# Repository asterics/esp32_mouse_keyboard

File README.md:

# ESP32 Mouse/Keyboard for BLE HID
ESP32 implementation for HID over GATT Keyboard and Mouse (Bluetooth Low Energy). Including serial API for external modules (compatible to Adafruit EZKey HID).

## Compatibility

Due to the wide variety of hardware & software combinations, it is hard to guarantee compatibility.
Nevertheless, we try to test this project with as much devices as possible.

Tested devices by the AsTeRICS team:

|    Device    | Mouse | Keyboard |
|--------------|-------|----------|
|PC with CSR 4.0 BT dongle, Debian Bullseye | yes | yes |
|Lenovo T440s, Debian Buster | yes | yes |
|MacBook Pro (Mid 2012) - macOS Mojave 10.14 | yes | yes |
|PC with CSR 4.0 BT dongle, Win10 Build 2004 | yes | yes |
|Lenovo T440s, Win10 Build 2004 in VirtualBox | no | no |
|Xiaomi Mi A1 - LineageOS 16.0 (Android 9) | yes | yes |
|Asus Nexus 7 (2013) - Android 6.0.1 | yes | yes | 
|iPad Air 2 (MGL12FD/A9 - iOS 13.3.1 | yes (Assistive Touch) | yes (Text input & accessible switch interface) |
|iPad Air 2 (MGL12FD/A9 - iOS 13.5.1 | yes (Assistive Touch) | yes (Text input & accessible switch interface) |
|iPad Pro 10.5" (MPHG2TY/A) - iOS 13.5.1 | yes (Assistive Touch) | yes (Text input & accessible switch interface) |
|iPad 6th Gen (MR7J2FD/A) - iOS 13.5.1 | yes (Assistive Touch) | yes (Text input & accessible switch interface) |

_Note:_ On some iPad devices, there might show up a notification in the Bluetooth menu, that this device may affect WiFi or Bluetooth performance.
You could ignore this error, according to [StackOverflow](https://apple.stackexchange.com/questions/386589/what-does-using-mx-anywhere-2s-may-affect-wi-fi-and-bluetooth-connectivity-mea) there is no clear
reason for this message, maybe it is related to the additional WiFi interface of the ESP32 (other user report this error if a normal mouse has an additional USB-dongle).

_Note:_ If you can report the compatibility status for a device, we would be happy to add a list of community tested devices, just open an issue with the label __device-testreport__.

## Building the ESP32 firmware

Please follow the step-by-step instructions of Espressif's ESP-IDF manual to setup the build infrastructure:
[Setup Toolchain](https://esp-idf.readthedocs.io/en/latest/get-started/index.html#setup-toolchain)

With `idf.py build` or `make` you can build this project.

With `idf.py -p (PORT) flash` or `make flash` you can upload this build to an ESP32

With `idf.py -p (PORT) monitor` or `make monitor` you can see the debug output (please use this output if you open an issue) or trigger basic test commands (mouse movement or a keyboard key press) on
a connected target.

__Note: Currently tested IDF version: release/v5.0 (other ones won't be supported!)__

### esp32miniBT vs. Arduino Nano Connect

This firmware is used on 2 different devices in context of our assistive devices:
* __esp32miniBT module__: This board is located in this repository and is used as addon for v2 FLipMouse, FABI and FLipPad PCBs which use either a TeensyLC or a ProMicro controller.
* __Arduino Nano RP2040 Connect__: Version 3 of FLipMouse and FLipPad (maybe FABI as well) use this Arduino board, where we have a RP2040 controller AND the ESP32 on the same board (more RAM, more flash, cheaper than 2 boards).

__Note:__ Please select the correct type of board in `idf.py menuconfig`!

__Note:__ If you want to use this firmware on a custom board, you can select the external UART interface settings in menuconfig; for our boards the pinning, baudrate and UART config is pre-defined.

# Usage via Console or second UART

## Control via stdin (make monitor)

For basic mouse and keyboard testing, some Bluetooth HID reports can be triggered via the 
keyboard when the make monitor console is running (see Espressif IDF docs: https://docs.espressif.com/projects/esp-idf/en/latest/api-guides/tools/idf-monitor.html ).

|Key|Function   |Description|
|---|-----------|-----------|
|a  |Mouse left |Move mouse left by 30px (`MOUSE_SPEED` define) |
|s  |Mouse down |Move mouse down by 30px (`MOUSE_SPEED` define) |
|d  |Mouse right|Move mouse right by 30px (`MOUSE_SPEED` define) |
|w  |Mouse up   |Move mouse up by 30px (`MOUSE_SPEED` define) |
|l  |Click left |Mouse click right |
|r  |Click right|Mouse click left  |
|q  |Type 'y' (US layout)   |just for testing keyboard reports|

## Control via 2nd UART

This interface is primarily used to control mouse / keyboard activities via an external microcontroller.

### Commands

Each command is started with a '$' character, followed by a command name (uppercase letters) and a variable number of parameters.
A command must be terminated by a '\n' character (LF, ASCII value 10)!

_Note:_ We do not test these on a regular basis!

|Command|Function|Parameters|Description|
|-------|--------|----------|-----------|
|$ID|Get ID|--|Prints out the ID of this module (firmware version number)|
|$GP|Get BLE pairings|--|Prints out all paired devices' MAC adress. The order is used for DP as well, starting with 0|
|$GC|Get active BLE connections|--|Prints out connected paired devices' MAC adress. Ordered by connection occurance (first connected device is listed first)|
|$SW|Switch between devices|BT addr (001122334455)|Switch between connected devices, the given BT addr will receive the HID packets|
|$DP|Delete one pairing (or all) |number of pairing, given as ASCII-characer '0'-'9'|Deletes one pairing. The pairing number is determined by the command GP. If no parameter is given, all pairings are removed!|
|$PM|Set pairing mode|'0' / '1'|Enables (1) or disables (0) discovery/advertising and terminates an exisiting connection if enabled|
|$NAME|Set BLE device name|name as ASCII string|Set the device name to the given name. Restart required.|
|$UG|Initiating firmware update|--|Boot partition is set to 'factory', if available. Device is restarted and expects firmware (.bin) via UART2|
|$SV|Set a key/value pair |key value| Set a value to ESP32 NVS storage, e.g. "$SV testkey This is a testvalue". Note: no spaces in the key! Returns "OK xx/yy used/free" on success, NVS:"error code" otherwise.|
|$GV|Get a key/value pair |key| Get a value from ESP32 NVS storage, e.g. "$GV testkey". Note: no spaces in the key!|
|$CV|Clear all key/value pairs |--| Delete all stored key/value pairs from $SV.|

### HID input

We use a format which is compatible to the Adafruit EZKey module, and added a few backwards compatible features.

__Mouse:__

|Byte 0|Byte 1|Byte 2|Byte 3|Byte 4|Byte 5|Byte 6|Byte 7|Byte 8|
|------|------|------|------|------|------|------|------|------|
| 0xFD | don't care | 0x03 | button mask | X-axis | Y-axis | wheel | don't care | don't care |

__Keyboard:__

_Note:_ currently we only support the US keyboard layout.

|Byte 0|Byte 1|Byte 2|Byte 3|Byte 4|Byte 5|Byte 6|Byte 7|Byte 8|
|------|------|------|------|------|------|------|------|------|
| 0xFD | modifier mask | 0x00   | keycode 1 | keycode 2 | keycode 3 | keycode 4 | keycode 5 | keycode 6 |

__Joystick:__

|Byte 0|Byte 1|Byte 2|Byte 3-8|Byte 9|Byte 10|Byte 11|Byte 12|Byte 13|
|------|------|------|------|------|------|------|------|------|
| 0xFD | don't care | 0x01  | X,Y,Z,Rz,Rx,Ry axis (each _int8_t_) | hat switch (0 is rest position; 1-8 are directions) | buttons 0-7 | buttons 8-15 | buttons 16-23 | buttons 24-31 |

## RAW HID input from sourcecode

If you want to change anything within the sourcecode, it is possible to send an HID report directly via:

```
hid_dev_send_report(hidd_le_env.gatt_if, hid_conn_id,
                  HID_RPT_ID_MOUSE_IN, HID_REPORT_TYPE_INPUT, HID_MOUSE_IN_RPT_LEN, mouse_report);
```

Use according `HID_RPT_ID_*`/`HID_*_IN_RPT_LEN`, depending on input type (mouse, keyboard).
The HID report data is located in array, passed as last parameter of `hid_dev_send_report`.

## Mouse & Keyboard input from sourcecode

Please use the functions provided by `esp_hidd_prf_api.c`.

## Credits and many thanks to:
- Paul Stoffregen for the implementation of the keyboard layouts for his Teensyduino project: www.pjrc.com
- Neil Kolban for his great contributions to the ESP32 SW (in particular the Bluetooth support): https://github.com/nkolban
- Chegewara for help and support

and to Espressif for providing the HID implementation within the esp-idf.

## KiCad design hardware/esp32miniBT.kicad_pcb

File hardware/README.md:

# esp32miniBT

The hardware module is an addon board for the FLipMouse or FABI device. It is placed on a separate module on the __AUX__ extension header.
This folder here contains the KiCAD design files for PCB production.

This design was done in KiCAD __v5.1.2__. Please use a version equal or newer.

__Note:__ If you are looking for the first revision of this board, open this [GIT tag](https://github.com/asterics/FLipMouse/tree/PCB_v0.3)

## Acknowledgements

* many thanks to asukiaaa for the esp32bb design and the footprints:
https://github.com/asukiaaa/esp32bb

* Junaid Akhter Khan for the second revision of the PCB

## Supported devices

* The FlipMouse is a universal finger- and mouth controller for mouse, keyboard, joystick and IR remote. Find more infos about the Flipmouse here: https://github.com/asterics/FLipMouse
* The FABI device is a switch interface for controlling mouse and keyboard in a versatile way: https://github.com/asterics/FABI

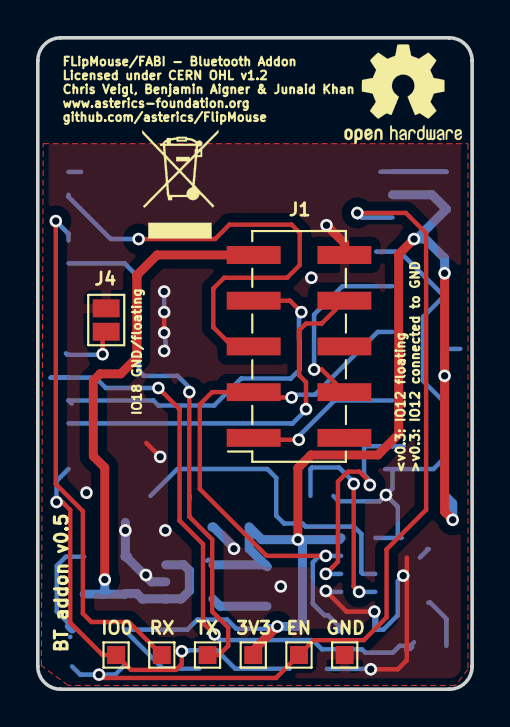
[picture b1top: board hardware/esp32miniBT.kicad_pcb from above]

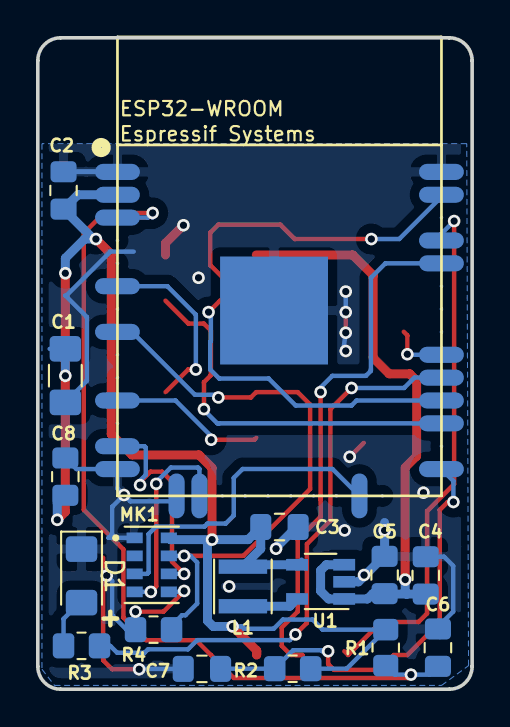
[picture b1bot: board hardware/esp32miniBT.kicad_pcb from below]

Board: 2 copper layers, 24.1 x 36.2 mm, 25 parts (17 on the bottom side), 20 nets.

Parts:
C1: 100uf; C_1206_3216Metric_Pad1.42x1.75mm_HandSolder
C2, C4, C6, C7, C8: 0.1uf; C_0805_2012Metric_Pad1.18x1.45mm_HandSolder
C3, C5: 10uf; C_0805_2012Metric_Pad1.18x1.45mm_HandSolder
D1: D05; LED_1206_3216Metric_Pad1.42x1.75mm_HandSolder
J1: Conn_02x05_Odd_Even; PinSocket_2x05_P2.54mm_Vertical_SMD
J4: SolderJumper_2_Open; SolderJumper-2_P1.3mm_Open_Pad1.0x1.5mm
L1: 4.7u / TYS30104R7M-10; L_Taiyo-Yuden_MD-3030
MK1: CMM-4030D-261-I2S-TR; MIC_CMM-4030D-261-I2S-TR
R1, R4: 100K; R_0805_2012Metric_Pad1.20x1.40mm_HandSolder
R2: 10k; R_0805_2012Metric_Pad1.20x1.40mm_HandSolder
R3: 330; R_0805_2012Metric_Pad1.20x1.40mm_HandSolder
TP1, TP2, TP3, TP4, TP5, TP6: TestPoint; TestPoint_Pad_1.0x1.0mm
U1: MCP1603T-330I/OS; TSOT-23-5
U2: ESP32-WROOM

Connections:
+3V3: C1.1, C2.1, C3.1, C8.1, L1.2, MK1.8, R1.1, R2.1, TP4.1, U1.4, U2.2
EN: C6.1, R1.2, TP5.1, U2.3
GND: C1.2, C2.2, C3.2, C4.2, C5.2, C6.2, C7.2, C8.2, D1.1, J1.10, J4.1, MK1.1, MK1.5, R4.2, TP6.1, U1.2, U2.1, U2.14, U2.15, U2.38, U2.39
IO0(boot): C7.1, R2.2, TP1.1, U2.25
IO5: R3.1, U2.29
IO13: MK1.4, U2.16
IO14: MK1.6, U2.13
IO15: MK1.3, U2.23
IO16: J1.8, U2.27
IO17: J1.7, U2.28
IO18: J4.2, U2.30
IO23: J1.5, U2.37
IO26: J1.1, U2.11
IO32: J1.3, MK1.7, R4.1, U2.8
IO34: J1.4, U2.6
unnamed: D1.2, R3.2
unnamed: L1.1, U1.5
RXDtoTXD0: TP2.1, U2.35
TXDtoRXD0: TP3.1, U2.34
VCC: C4.1, C5.1, J1.9, U1.1, U1.3

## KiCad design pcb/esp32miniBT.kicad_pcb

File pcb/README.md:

# ESP32miniBT Add-On-Board for the FlipMouse

Kicad project for a mini ESP32-based BLE daughterboard for the FlipMouse
Find the BOM in subfolder /docs

many thanks to asukiaaa for the esp32bb design and the footprints:
https://github.com/asukiaaa/esp32bb

The firmware for the ESP32 can be found here:
https://github.com/asterics/esp32_mouse_keyboard

The FlipMouse is a universal finger- and mouth controller for mouse, keyboard, joystich and IR remote
Find more infos about the Flipmouse here:
https://github.com/asterics/FLipMouse

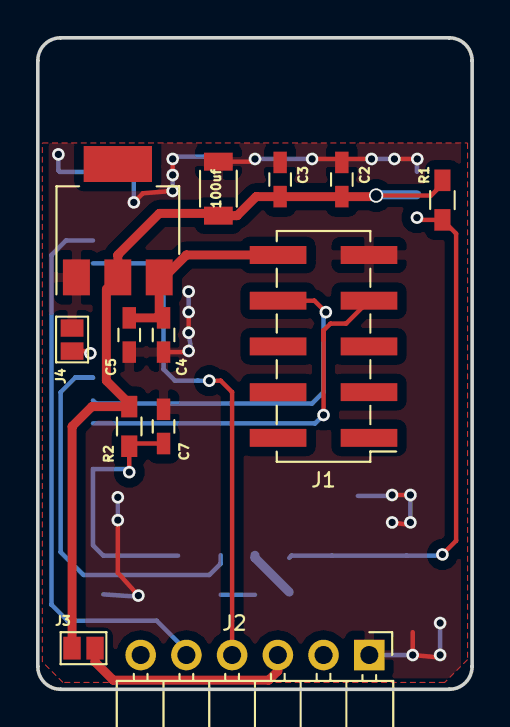
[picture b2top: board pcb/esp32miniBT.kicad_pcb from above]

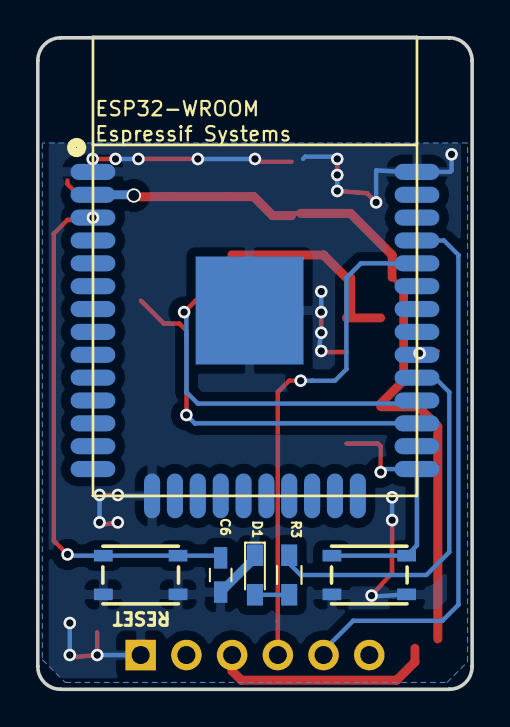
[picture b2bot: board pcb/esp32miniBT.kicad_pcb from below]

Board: 2 copper layers, 24.1 x 36.2 mm, 19 parts (6 on the bottom side), 13 nets.

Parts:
C1: 100uf; C_1206
C2, C4: 0.1uf; C_0603_HandSoldering
C3, C5: 10uf; C_0603_HandSoldering
C6, C7: 1nf; C_0603_HandSoldering
D1: D05; LED_0603_HandSoldering
J1: Conn_FlipMouse; Pin_Header_Straight_2x05_Pitch2.54mm_SMD
J2: Conn_01x06; Pin_Header_Angled_1x06_Pitch2.54mm
J3, J4: GS2
R1, R2: 10K; R_0603_HandSoldering
R3: 330; R_0603_HandSoldering
SW1, SW2: SWITCH_SPST; SKRPACE010
U1: U1; SOT-223
U2: ESP32-WROOM

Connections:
+3V3: C1.1, C2.1, C3.1, J3.1, R1.1, R2.1, U1.2, U2.2
EN: C6.1, R1.2, SW1.1, U2.3
GND: C1.2, C2.2, C3.2, C4.2, C5.2, C6.2, C7.2, D1.1, J1.9, J2.1, J4.1, SW1.2, SW2.2, U1.1, U2.1, U2.15, U2.38, U2.39
IO0(boot): C7.1, R2.2, SW2.1, U2.25
IO5: R3.1, U2.29
IO16: J1.7, U2.27
IO17: J1.8, U2.28
IO18: J4.2, U2.30
unnamed: D1.2, R3.2
unnamed: J2.3, J3.2
RXDtoTXD0: J2.5, U2.35
TXDtoRXD0: J2.4, U2.34
VCC: C4.1, C5.1, J1.10, U1.3

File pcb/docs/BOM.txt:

BOM for ESP32miniBT add-on module for FlipMouse
===============================================

U1:      Low-Dropout-Regulator 3,3V  (NCP1117ST33T)  Farnell 1825376
U2:      Espressiv             ESP32 (Wroom PCB)     Mouser: 356-ESP-WROOM-32  (or via ebay, aliexpress etc.)
C1:      Capacitor             100uf (0603)          Farnell: 2852775
C2,C4:   Capacitor             100nf (0603)          Farnell: 1327731
C3,C5:   Capacitor              10uf (0603)          Farnell: 2346889
C6,C7:   Capacitor               1nf (0603)          Farnell: 2280655
R1,R2:   Resistor                10k (0603)          Farnell: 2140192
R3:      Resistor                330 (0603)          Farnell: 2502447
D1:      LED SMD               green (0603)          Farnell: 2687486
Sw1,SW2: Switch SMD             KMR6 (2N)            Farnell: 2845721
J1:      Socketstrip  SMD        5x2 (2,54mm)        Farnell: 2293771
J2:      Pinheader               5x1 (2,54mm)        Farnell: 2356157

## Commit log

2017-11-16 First commit Working Keyboard and Mouse Untested: mouse via external serial interface TBD: Joystick
2017-11-17 Updates on README Added deadkey sending on KC Changed delay on console "Q" to wait BEFORE sending the key
2017-11-17 MD format update
2018-01-01 Update sdkconfig
2018-01-01 Fix .gitignore
2018-01-01 Fix deprecated header
2018-03-15 Updated sdkconfig to current esp-idf, changed XTAL freq to auto
2018-03-15 Updates on bonding& event handling, closing #5
2018-05-02 Changed to current GIT esp-idf. (removed bt_trace & LOG_ERROR/LOG_xxx)
2018-05-04 First commit of @nkolban 's code. Not working right now (see: https://github.com/nkolban/esp32-snippets/issues/230 )
2018-05-04 Changed cpp code according to new example by @nkolban
2018-05-04 Added joystick HID description to map, configurable via defines (mouse / joystick)
2018-05-04 Changed file header
2018-05-04 Enabled notifications, as suggested here #4
2018-05-07 Kbd is working, mouse is working on Linux & Android but NOT on Windows
2018-05-08 Added "." to include dir, allow using keyboard.h
2018-05-14 Cleanup & added variable HID report map
2018-05-14 Removed unused HID descriptor
2018-05-16 Added EZKey compatibility, WARNING: changed to external UART
2018-05-18 Restart advertising on client disconnect CB
2018-05-30 modified parser (ASCII-commands, 2 UARTS, bug removal), updated IDF verison and readme
2018-06-20 Set auth mode to none, but added encryption to access permissions of characteristics. Maybe fixes iOS problems.
2018-06-20 As suggested by chegewara, all 2902's are set to request encryption before they are used. All 2908 are set to encryption as well
2018-06-27 added indicator led and configurable devicename
2018-06-27 added KiCad files for FlipMouse add-on PCB
2018-12-03 fix error
    fix this error -> error: enumeration value 'ESP_GATTS_SEND_SERVICE_CHANGE_EVT' not handled in switch [-Werror=switch]
2020-01-16 Removed Neil Kolbans lib, added Espressif stack
2020-02-13 Removed sdkconfig & added default values
2020-02-13 Added sdkconfig/sdkconfig.old to git ignore
2020-02-13 Removed Neil Kolbans Utils
2020-02-16 Added absolute mouse HID descriptor, untested!
2020-02-16 Added '$' into command description, added description of RAW HID sending, fixed link to idf-monitor
2020-02-16 Added test code for sending absolute mouse reports (directly, via numpad keys: 0 click, 1-9 positioning)
2020-02-18 Added an HID report for absolute mouse.
2020-03-05 Added CMakefiles, changed project name. Closing #31
2020-04-05 added build infos to Readme
2020-05-28 Fixed win10 driver error problem ("code 10"), suggestions by Espressif BLE HOG example.
    Windows is much more picky regarding unused GATT attributes.
    In our case, there was a HID vendor report included, which
    was triggering the problem. The keyboard LED report was removed too.
2020-05-29 Added working Joystick support
2020-06-05 A few changes, nothing working well...
2020-06-05 Re implemented Boot KBD out
2020-06-23 Re-adapted the Espressif HID example, changes to the original example:
    * Added UART interface
    * Added mouse wheel
    * Added blink task
2020-06-23 Changed MTU to 23 Bytes (for the damn iOS), changed min_interval
2020-06-23 Fixed undocumented Apple "Feature": accessible switch interface works only if keyboard report is first in report map.
2020-06-25 Do not change MTU to 23Bytes.
2020-06-25 Removed partitions.csv, not needed here.
2020-06-25 Updated readme, added compatibility infos
2020-06-25 Changed iPad Air iOS version, added hint for MOUSE_SPEED macro
2020-06-29 Added CMakeLists file for CMake builds
2020-06-29 Added a KConfig file for future configuration settings (currently unused!)
2020-07-02 Preparation for pairing on/off (see #36) & formatting with astyle.
    Note that currently it is not possible to activate the pairing on/off option,
    because it is broken in the esp-idf.
2020-07-02 Using KConfig variables for pin numbers, BT device name.
2020-07-17 Implemented rate limiter for HID reports.
    Added new config variables for KConfig:
    -) enabling rate limiter
    -) set interval in microseconds
    -) Either accumulate mouse movements or discard reports when sent too fast
2020-07-17 Added joystick interface & using configuration
2020-07-17 Added joystick support
2020-07-20 Changed rate limiter notification to verbose
2020-07-20 Added notes on accumulate recommendation, added mouse button change tracker
2020-07-20 Fixed the Keyboard Output Report for receiving Caps&Num Lock updates (LED report), closing #38 : - Added report ID for LEDs - Added callback event type for LED - Fixed the characteristic & added writ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
2020-07-20 Added test buttons for consumer control keys
2020-07-20 Moved all the rate limiter stuff into the esp_hidd_prf_api files, accumulate mode not finished! Implemented a timer based solution for accumulating mode.
2020-07-21 working rate limiter with accumulate: - moved to esp_hidd_prf_api.c - changed default values for time interval in KConfig - Implemented rate limiter callback - Fixed signed int8 problem - Synchronizi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
2020-07-26 Encrypt GATT permissions
2020-07-26 Ignore .vscode folder
2020-07-27 Added passkey command
2020-07-29 Forcing ENC_MITM on characteristics
2020-08-06 Added MBPro Mojave as working device
2020-08-06 Changed rate limiter default to accumulate. Removed "NOT RECOMMENDED" from KConfig
2020-08-10 Changed IO capabilites to yes/no -> added numerical comparison handling which is answered with "Yes" all the time (no more user input necessary)
2020-08-10 Changed ENC_MITM to ENCRYPTED
2020-08-10 Changed auth request to MITM with bonding, on GATTS connect request a MITM protection
2020-08-10 Added @rampadc to contributors
2020-08-11 Removed the PCB files, can be found in https://github.com/asterics/FLipMouse/tree/master/Hardware/Addons/BT-module
2020-10-11 Added remaining parts of external cmd processing (return channel), especially for Bluetooth pairing management ($DP / $GP)
2020-11-10 Closing #44, THX to Lars-Thestorf
2020-12-01 Added connection switch & name resolution
2020-12-01 Added $SW to command list.
2021-04-13 Added RX/TX autodetection with internal pull-down resistor.
2021-04-13 Added 1 tick delay for activating pull-down
2021-04-13 Removed unused weak declaration
2021-04-14 Impplementation of command - initiating restart into factory partition
2021-04-14 First $GV/$SV draft.
2021-04-15 Added used/free output
2021-04-15 Readme file updated
2021-04-16 Fixed core panic if no value is provided to $SV & changed a few lines to compile successfully
2021-04-16 Added $CV to clear all key/value pairs
2021-04-16 Added commands to README
2021-04-16 Uncommented device detection
2021-04-19 Fixed strlen error
2021-04-19 Small adaptions of feedback for $UG (adding "OTA:" prefix)
2021-04-30 Improved cursor control by updating the connection interval on connect
2021-05-03 Removed debug output of mouse coordinates
2021-05-05 Added an idle timer to sent empty packets to keep connection "prioritized"
2021-05-28 Enable full range of GPIOs for UARTs and LEDs
2021-06-21 Added doxygen generator config
2021-06-21 Added esp32miniBT PCB (current version from FLipMouse)
2021-06-21 * changed LDO to DCDC (avoiding problems with low USB voltage) * changed IO0 pullup to 10k (avoiding problems with download mode on some ESP32 revisions) * added PDF
2021-06-24 Changed version string for v0.3 release
2021-08-18 Added 3D Design for the programming adapter with pogopins
2021-09-22 Updated interactive BOM, 2 versions (LDO & DC/DC)
2021-09-22 added new interactive BOM
2021-11-19 Added MEMS microphone speech recognition to README, implementation TBD
2021-11-23 Added I2S audio streaming to a websocket for STT. Still not working completely!
2021-11-25 Microphone basically working!
2021-12-13 Fixed CMakeLists.txt, closing #54
2021-12-15 Added sending the recognized words via UART (TBD: parsing to HID on FABI/FM)
2022-01-07 Changed appearance to mouse, closing #52
2022-01-24 Changed version string to v0.3.2
2022-01-24 Changed hid_conn_id to be used only if a dedicated device should be used ("§SW"), otherwise all connected devices receive the input
2022-01-25 BUG: disconnected parameter were written to connect parameter union.
2022-01-25 Added helper functions for determining active connections & code cleanup
2022-01-25 Debug serial port: go back to default mode after entering a "$xxx" command
2022-02-22 Added info on deleting all pairings
2022-08-02 Changed flash size to 2MB in default config
2022-08-02 Removed CMake requirements
2022-08-02 Changed KConfig and some main code to support the Arduino Nano RP2040 connect board
2022-08-04 Changed version string, updated README
2022-09-05 Added joystick to HID report map; removed SUPPORT_VENDOR
2022-09-07 Added high level functions to send the joystick report; added comments in hidd api
2022-09-07 Added joystick functions in main code; added API in README
2023-02-08 Added idf v5 compatibility
2023-02-08 Added compatibility code to use this firmware on addon boards and the Arduino RP2040 Connect
2023-02-09 Fixed UART clock error due to idf v5 upgrade; added sdkconfig defaults for detecting flash size
2023-02-10 Small update
2023-02-10 Fixed compile error with joystick data array; enabled joystick in sdkconfig.defaults
2023-02-10 Working bluetooth joystick & cleanup:
    -) added joystick axis & button to simple tests (keys 1,2,3,4)
    -) fixed log output of joystick report
    -) changed hid_add_id_tbl table creation, use variable as index
    -) fixe HIDD_LE_IDX_REPORT_JOY_IN_CHAR (and similar) enum, consumer control was on the wrong position
2023-02-10 Fixed joystick buttons
2023-02-10 Changed version string
2023-02-15 Stripped down HID report map; still no luck with win10
2023-02-15 Fixed for esp-idf v4. Warning: this code does not work with idf v5 + windows, no idea why...
2023-02-15 Fixed UART clock rate for esp-idf v5
2023-02-15 Added note on supported IDF
2023-02-15 Changed HID report map; windows is VERY picky (works on Android & Linux, but driver error in Win10)
2023-02-16 Changed connection interval for iOS "devices".
2023-02-16 joystick can be enabled/disabled on the fly with $JP0 / $JP1: * fixed indentations in command overview * added $JP command & corresponding field in config struct & NVS storage * added the flag for en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
2023-03-02 Changed version string to v0.3.6
2023-07-03 Set BLE TX level low, trying to avoid interference on Arduino RP2040 connect
2024-03-26 module type must be selected on compilation now (either esp32_miniBT or Arduino Nano RP2040 Connect); fixed linking error with BLE & esp idf 5
2024-03-26 Added BT4.2 features, avoid linker errors in esp-idf >= 5

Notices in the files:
hardware/esp32miniBT.kicad_pcb:
Licensed under CERN OHL v1.2
